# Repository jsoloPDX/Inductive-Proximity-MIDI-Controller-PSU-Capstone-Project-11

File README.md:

# MIDI-THEREMIN-Controller
A theremin style controller for MIDI devices
A Senior ECE practicum project for Portland State University

Background

Most electronic musical instruments are controlled by small motions such as knob-turns or button-pushes. Such actions tend to be neither as interesting to watch nor as expressive as, for example, a guitarist strumming or a drummer drumming (or a piper piping). Using hand gestures and arm motions to control musical instruments would allow more precise and expressive control of electronic instrument parameters. The theremin, an analog electronic instrument can be controlled by hand gestures, but it’s ability to interface with modern equipment is lacking and or restrictive.

Objective

Our objective is to update the Theremin-style analog instrument to contain digital features, mainly a MIDI output. This will allow it to expressively control all kinds of modern musical instruments and equipment.

HOW IT SHOULD WORK:
An analog theremin circuit will send proximity information to a Microcontroller. The Microcontroller will organize, process, and convert that information into MIDI data, which will be sent to a MIDI capable device VIA a standard MIDI or USB MIDI connector. There is some room for automation as far as built in “calibration” sequences to adjust the sensitivity of the coils. The device will be somewhat modular in design and construction, which will allow for expansion of the variety of proximity sensors used and versatility of output signals.

The code library "Arduino_MIDI_Library_v4.2.zip" is not our work and is taken from the project at: https://github.com/FortySevenEffects/arduino_midi_library/

The EagleCAD library "adafruit-Adafruit-Eagle-Library-4abf84c.zip" is not our work and is taken from the project at:
https://github.com/adafruit/Adafruit-Eagle-Library

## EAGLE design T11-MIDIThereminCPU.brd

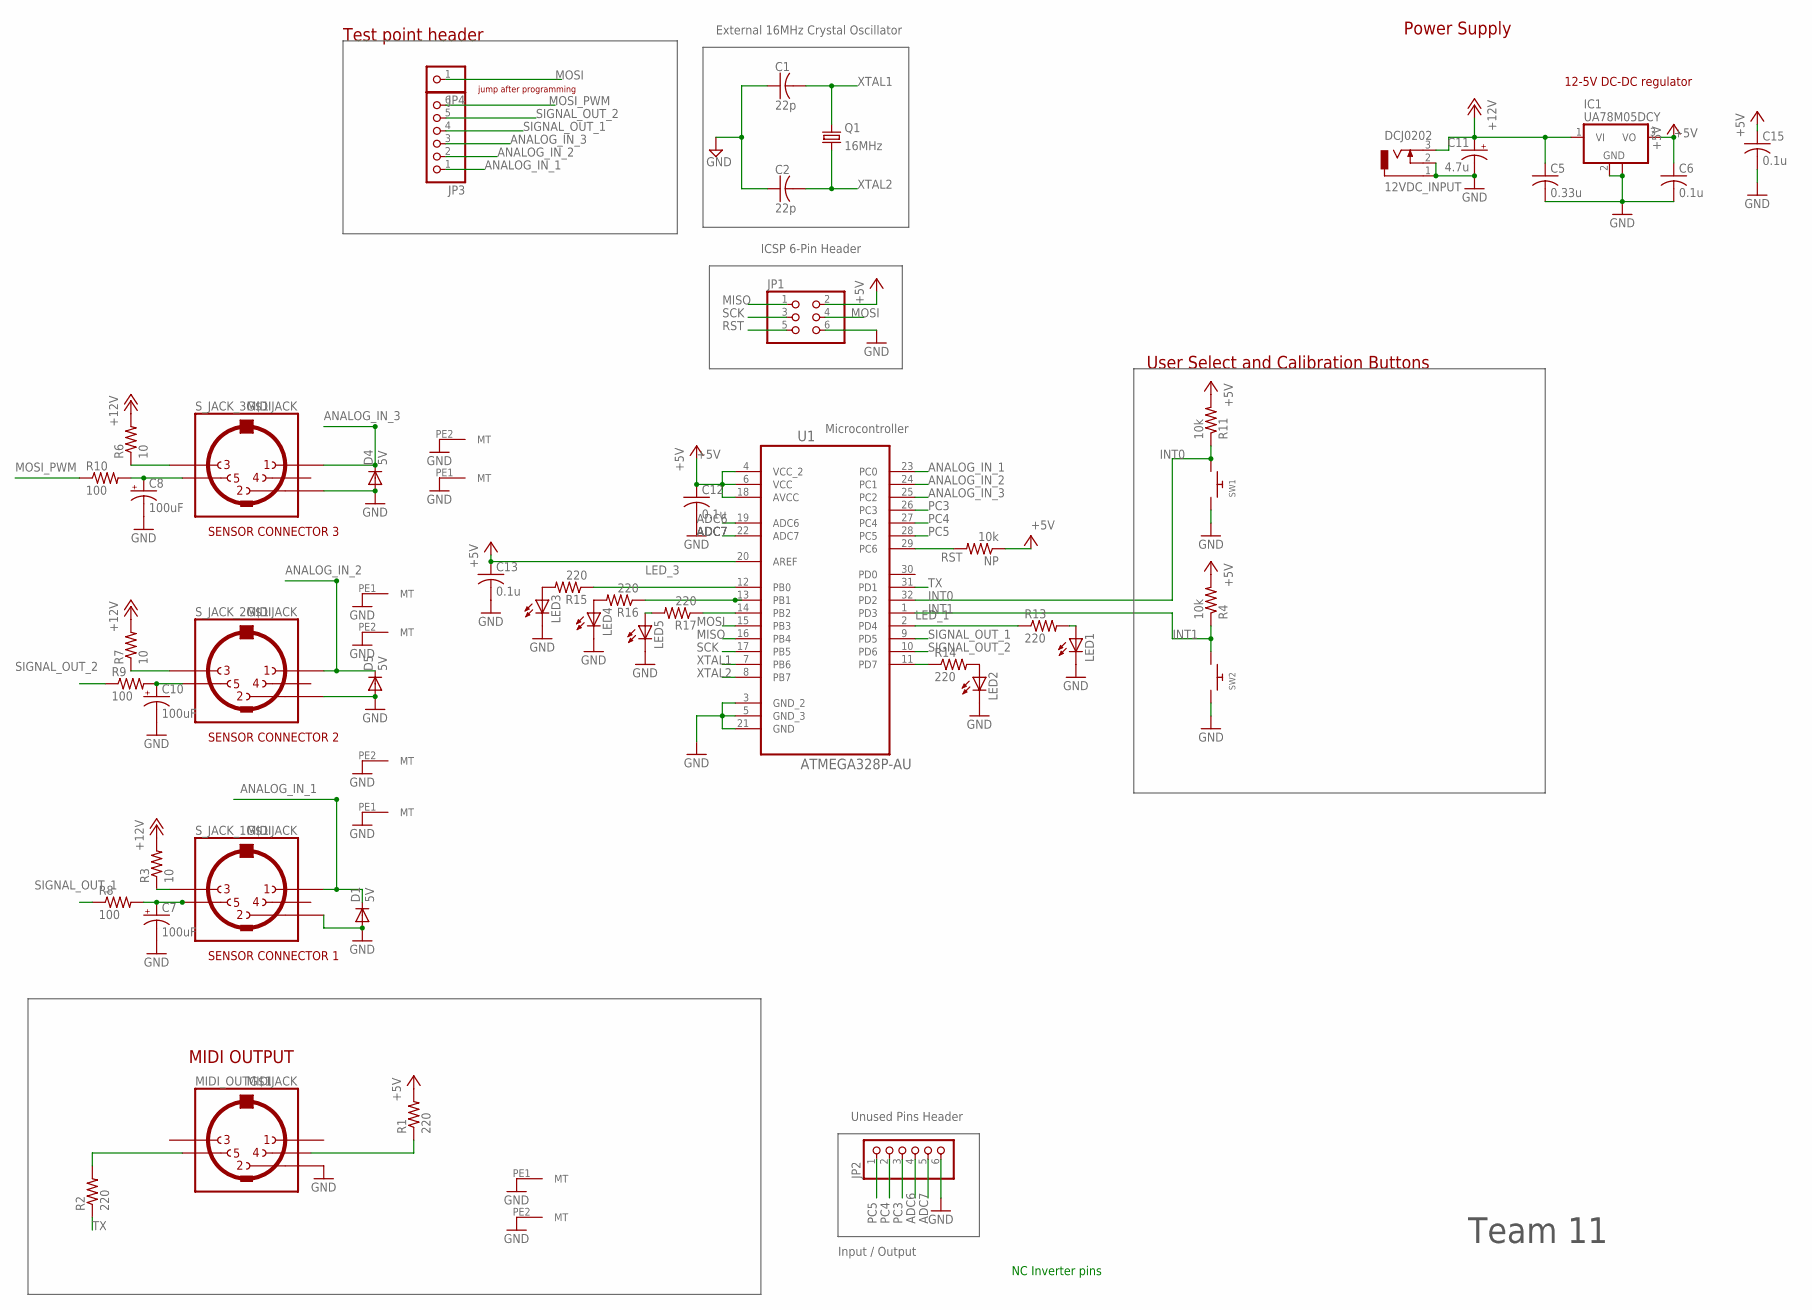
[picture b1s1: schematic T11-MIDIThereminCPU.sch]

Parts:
12VDC_INPUT: DCJ0202
C1, C2: 22p; C0805
C5: 0.33u; C0805
C6, C12, C13, C15: 0.1u; C0805
C7, C8, C10: 100uF; E3,5-8
C11: 4.7u; E3,5-8
D1, D4, D5: 5V; DO35-7
IC1: UA78M05DCY; SOT223
JP1: PINHD-2X3; 2X03
JP2, JP3: PINHD-1X6; 1X06
JP4: PINHD-1X1; 1X01
LED1, LED2, LED3, LED4, LED5: LED3MM
MIDI_OUT: MIDIJACK; CP-2350
NP: 10k; R0805
Q1: 16MHz; SM49
R1, R13, R14, R15, R16, R17: 220; R0805
R2: 220; M0805
R3, R7: 10; R0805
R4, R11: 10k; R0805
R6: 10; M0805
R8, R9: 100; R0805
R10: 100; M0805
SW1, SW2: SWITCH_PUSHBUTTONSOFTTOUCHSMD_SJ; PUSHBUTTON_SMD_SJ
S_JACK_1, S_JACK_2, S_JACK_3: MIDIJACK; CP-2350
U1: ATMEGA328P-AU; QFP80P900X900X120-32N

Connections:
+5V: C6.1, C12.1, C13.1, C15.1, IC1.3 (VO), JP1.2, NP.1, R1.2, R4.2, R11.2, U1.4 (VCC_2), U1.6 (VCC), U1.18 (AVCC), U1.20 (AREF)
+12V: 12VDC_INPUT.3, C5.1, C11.+, IC1.1 (VI), R3.2, R6.2, R7.2
ADC6: JP2.4, U1.19 (ADC6)
ADC7: JP2.5, U1.22 (ADC7)
ANALOG_IN_1: D1.C, JP3.1, S_JACK_1.1, U1.23 (PC0)
ANALOG_IN_2: D5.C, JP3.2, S_JACK_2.1, U1.24 (PC1)
ANALOG_IN_3: D4.C, JP3.3, S_JACK_3.1, U1.25 (PC2)
GND: 12VDC_INPUT.1, 12VDC_INPUT.2, C1.1, C2.1, C5.2, C6.2, C7.-, C8.-, C10.-, C11.-, C12.2, C13.2, C15.2, D1.A, D4.A, D5.A, IC1.2 (GND), IC1.4 (GND), JP1.6, JP2.6, LED1.K (C), LED2.K (C), LED3.K (C), LED4.K (C), LED5.K (C), MIDI_OUT.2, MIDI_OUT.PE1 (MT), MIDI_OUT.PE2 (MT), SW1.P$1, SW2.P$1, S_JACK_1.2, S_JACK_1.PE1 (MT), S_JACK_1.PE2 (MT), S_JACK_2.2, S_JACK_2.PE1 (MT), S_JACK_2.PE2 (MT), S_JACK_3.2, S_JACK_3.PE1 (MT), S_JACK_3.PE2 (MT), U1.3 (GND_2), U1.5 (GND_3), U1.21 (GND); also elsewhere on the board
INT0: R11.1, SW1.P$2, U1.32 (PD2); also elsewhere on the board
INT1: R4.1, SW2.P$2, U1.1 (PD3); also elsewhere on the board
LED_1: R13.1, U1.2 (PD4)
LED_2: R14.1, U1.11 (PD7)
LED_3: R15.1, U1.12 (PB0)
LED_4: R16.1, U1.13 (PB1)
LED_5: R17.1, U1.14 (PB2)
MISO: JP1.1, U1.16 (PB4)
MOSI: JP1.4, JP4.1, U1.15 (PB3)
MOSI_PWM: JP3.6, R10.1
unnamed: MIDI_OUT.4, R1.1
unnamed: C8.+, R10.2, S_JACK_3.5
unnamed: LED1.A, R13.2
unnamed: R6.1, S_JACK_3.3
unnamed: LED2.A, R14.2
unnamed: C10.+, R9.2, S_JACK_2.5
unnamed: R3.1, S_JACK_1.3
unnamed: MIDI_OUT.5, R2.2
unnamed: LED3.A, R15.2
unnamed: LED4.A, R16.2
unnamed: LED5.A, R17.2
unnamed: R7.1, S_JACK_2.3
unnamed: C7.+, R8.2, S_JACK_1.5
PC3: JP2.3, U1.26 (PC3)
PC4: JP2.2, U1.27 (PC4)
PC5: JP2.1, U1.28 (PC5)
RST: JP1.5, NP.2, U1.29 (PC6)
SCK: JP1.3, U1.17 (PB5)
SIGNAL_OUT_1: JP3.4, R8.1, U1.9 (PD5)
SIGNAL_OUT_2: JP3.5, R9.1, U1.10 (PD6)
TX: R2.1, U1.31 (PD1)
XTAL1: C1.2, Q1.2, U1.7 (PB6)
XTAL2: C2.2, Q1.1, U1.8 (PB7)

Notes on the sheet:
External 16MHz Crystal Oscillator
ICSP 6-Pin Header
Power Supply
SENSOR CONNECTOR 1
MIDI OUTPUT
Input / Output
User Select and Calibration Buttons
Unused Pins Header
Test point header
Team 11
12-5V DC-DC regulator
Microcontroller
NC Inverter pins
SENSOR CONNECTOR 2
SENSOR CONNECTOR 3
jump after programming

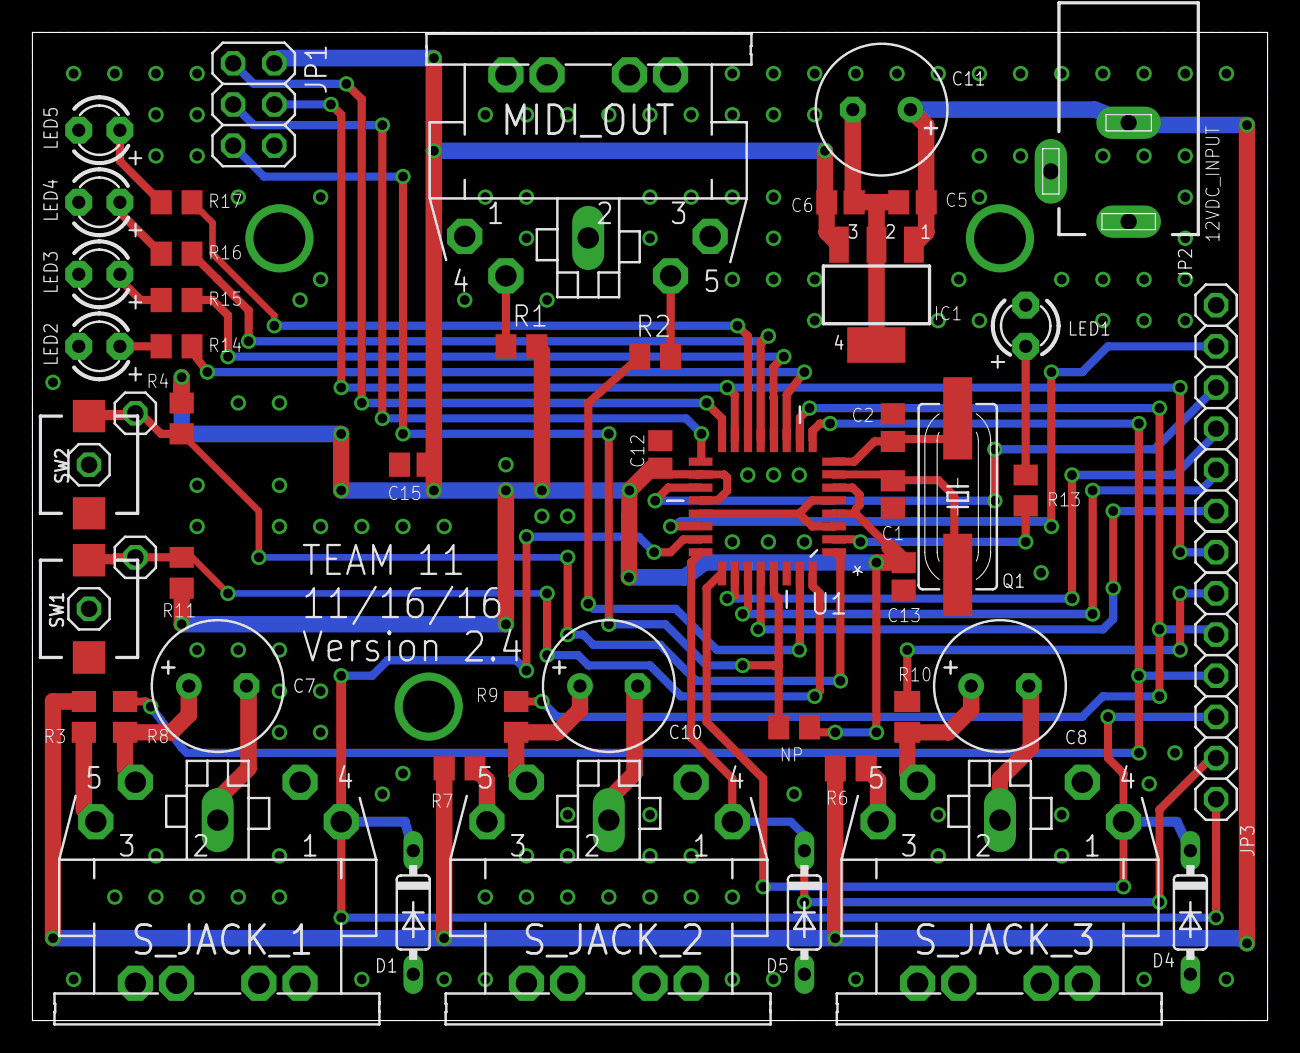
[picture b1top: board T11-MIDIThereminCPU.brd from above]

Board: 2 copper layers, 76.2 x 61.0 mm, 53 parts (0 on the bottom side), 41 nets.

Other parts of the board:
JP5, JP6, JP7, JP8: 1X01

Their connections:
GND: JP6.1, JP8.1; also elsewhere on the board
INT0: JP5.1; also elsewhere on the board
INT1: JP7.1; also elsewhere on the board

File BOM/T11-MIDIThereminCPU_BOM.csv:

"Part";"Value";"Device";"Package";"Description";"MF";"MPN";"OC_FARNELL";"OC_NEWARK";"PACKAGE";"SUPPLIER";
"12VDC_INPUT";"DCJ0202";"DCJ0202";"DCJ0202";"DC POWER JACK";"";"";"unknown";"unknown";"";"";
"C1";"22p";"C-USC0805";"C0805";"CAPACITOR, American symbol";"";"";"";"";"";"";
"C2";"22p";"C-USC0805";"C0805";"CAPACITOR, American symbol";"";"";"";"";"";"";
"C5";"0.33u";"C-USC0805";"C0805";"CAPACITOR, American symbol";"";"";"";"";"";"";
"C6";"0.1u";"C-USC0805";"C0805";"CAPACITOR, American symbol";"";"";"";"";"";"";
"C7";"100uF";"CPOL-USE3.5-8";"E3,5-8";"POLARIZED CAPACITOR, American symbol";"";"";"";"";"";"";
"C8";"100uF";"CPOL-USE3.5-8";"E3,5-8";"POLARIZED CAPACITOR, American symbol";"";"";"";"";"";"";
"C10";"100uF";"CPOL-USE3.5-8";"E3,5-8";"POLARIZED CAPACITOR, American symbol";"";"";"";"";"";"";
"C11";"4.7u";"CPOL-USE3.5-8";"E3,5-8";"POLARIZED CAPACITOR, American symbol";"";"";"";"";"";"";
"C12";"0.1u";"C-USC0805";"C0805";"CAPACITOR, American symbol";"";"";"";"";"";"";
"C13";"0.1u";"C-USC0805";"C0805";"CAPACITOR, American symbol";"";"";"";"";"";"";
"C15";"0.1u";"C-USC0805";"C0805";"CAPACITOR, American symbol";"";"";"";"";"";"";
"D1";"5V";"1N4148DO35-7";"DO35-7";"DIODE";"";"";"";"";"";"";
"D4";"5V";"1N4148DO35-7";"DO35-7";"DIODE";"";"";"";"";"";"";
"D5";"5V";"1N4148DO35-7";"DO35-7";"DIODE";"";"";"";"";"";"";
"IC1";"UA78M05DCY";"UA78M05DCY";"SOT223";"POSITIVE-VOLTAGE REGULATORS";"";"";"";"";"";"";
"JP1";"";"PINHD-2X3";"2X03";"PIN HEADER";"";"";"";"";"";"";
"JP2";"";"PINHD-1X6";"1X06";"PIN HEADER";"";"";"";"";"";"";
"JP3";"";"PINHD-1X6";"1X06";"PIN HEADER";"";"";"";"";"";"";
"JP4";"";"PINHD-1X1";"1X01";"PIN HEADER";"";"";"";"";"";"";
"JP5";"";"PINHD-1X1";"1X01";"PIN HEADER";"";"";"";"";"";"";
"JP6";"";"PINHD-1X1";"1X01";"PIN HEADER";"";"";"";"";"";"";
"JP7";"";"PINHD-1X1";"1X01";"PIN HEADER";"";"";"";"";"";"";
"JP8";"";"PINHD-1X1";"1X01";"PIN HEADER";"";"";"";"";"";"";
"LED1";"";"LED3MM";"LED3MM";"LED";"";"";"";"";"";"";
"LED2";"";"LED3MM";"LED3MM";"LED";"";"";"";"";"";"";
"LED3";"";"LED3MM";"LED3MM";"LED";"";"";"";"";"";"";
"LED4";"";"LED3MM";"LED3MM";"LED";"";"";"";"";"";"";
"LED5";"";"LED3MM";"LED3MM";"LED";"";"";"";"";"";"";
"MIDI_OUT";"MIDIJACK";"MIDIJACK";"CP-2350";"DIN 5 jack also known as MIDI jack";"";"";"";"";"";"";
"NP";"10k";"R-US_R0805";"R0805";"RESISTOR, American symbol";"";"";"";"";"";"";
"Q1";"16MHz";"CRYSTALSM49";"SM49";"CRYSTAL";"";"";"unknown";"unknown";"";"";
"R1";"220";"R-US_R0805";"R0805";"RESISTOR, American symbol";"";"";"";"";"";"";
"R2";"220";"R-US_M0805";"M0805";"RESISTOR, American symbol";"";"";"";"";"";"";
"R3";"10";"R-US_R0805";"R0805";"RESISTOR, American symbol";"";"";"";"";"";"";
"R4";"10k";"R-US_R0805";"R0805";"RESISTOR, American symbol";"";"";"";"";"";"";
"R6";"10";"R-US_M0805";"M0805";"RESISTOR, American symbol";"";"";"";"";"";"";
"R7";"10";"R-US_R0805";"R0805";"RESISTOR, American symbol";"";"";"";"";"";"";
"R8";"100";"R-US_R0805";"R0805";"RESISTOR, American symbol";"";"";"";"";"";"";
"R9";"100";"R-US_R0805";"R0805";"RESISTOR, American symbol";"";"";"";"";"";"";
"R10";"100";"R-US_M0805";"M0805";"RESISTOR, American symbol";"";"";"";"";"";"";
"R11";"10k";"R-US_R0805";"R0805";"RESISTOR, American symbol";"";"";"";"";"";"";
"R13";"220";"R-US_R0805";"R0805";"RESISTOR, American symbol";"";"";"";"";"";"";
"R14";"220";"R-US_R0805";"R0805";"RESISTOR, American symbol";"";"";"";"";"";"";
"R15";"220";"R-US_R0805";"R0805";"RESISTOR, American symbol";"";"";"";"";"";"";
"R16";"220";"R-US_R0805";"R0805";"RESISTOR, American symbol";"";"";"";"";"";"";
"R17";"220";"R-US_R0805";"R0805";"RESISTOR, American symbol";"";"";"";"";"";"";
"SW1";"";"SWITCH_PUSHBUTTONSOFTTOUCHSMD_SJ";"PUSHBUTTON_SMD_SJ";"Buttons";"";"";"";"";"";"";
"SW2";"";"SWITCH_PUSHBUTTONSOFTTOUCHSMD_SJ";"PUSHBUTTON_SMD_SJ";"Buttons";"";"";"";"";"";"";
"S_JACK_1";"MIDIJACK";"MIDIJACK";"CP-2350";"DIN 5 jack also known as MIDI jack";"";"";"";"";"";"";
"S_JACK_2";"MIDIJACK";"MIDIJACK";"CP-2350";"DIN 5 jack also known as MIDI jack";"";"";"";"";"";"";
"S_JACK_3";"MIDIJACK";"MIDIJACK";"CP-2350";"DIN 5 jack also known as MIDI jack";"";"";"";"";"";"";
"U1";"ATMEGA328P-AU";"ATMEGA328P-AU";"QFP80P900X900X120-32N";"8-bit Microcontroller with In-System Programmable Flash";"";"ATMEGA328P-AU";"1715486";"14R4631";"TQFP-32";"Atmel";

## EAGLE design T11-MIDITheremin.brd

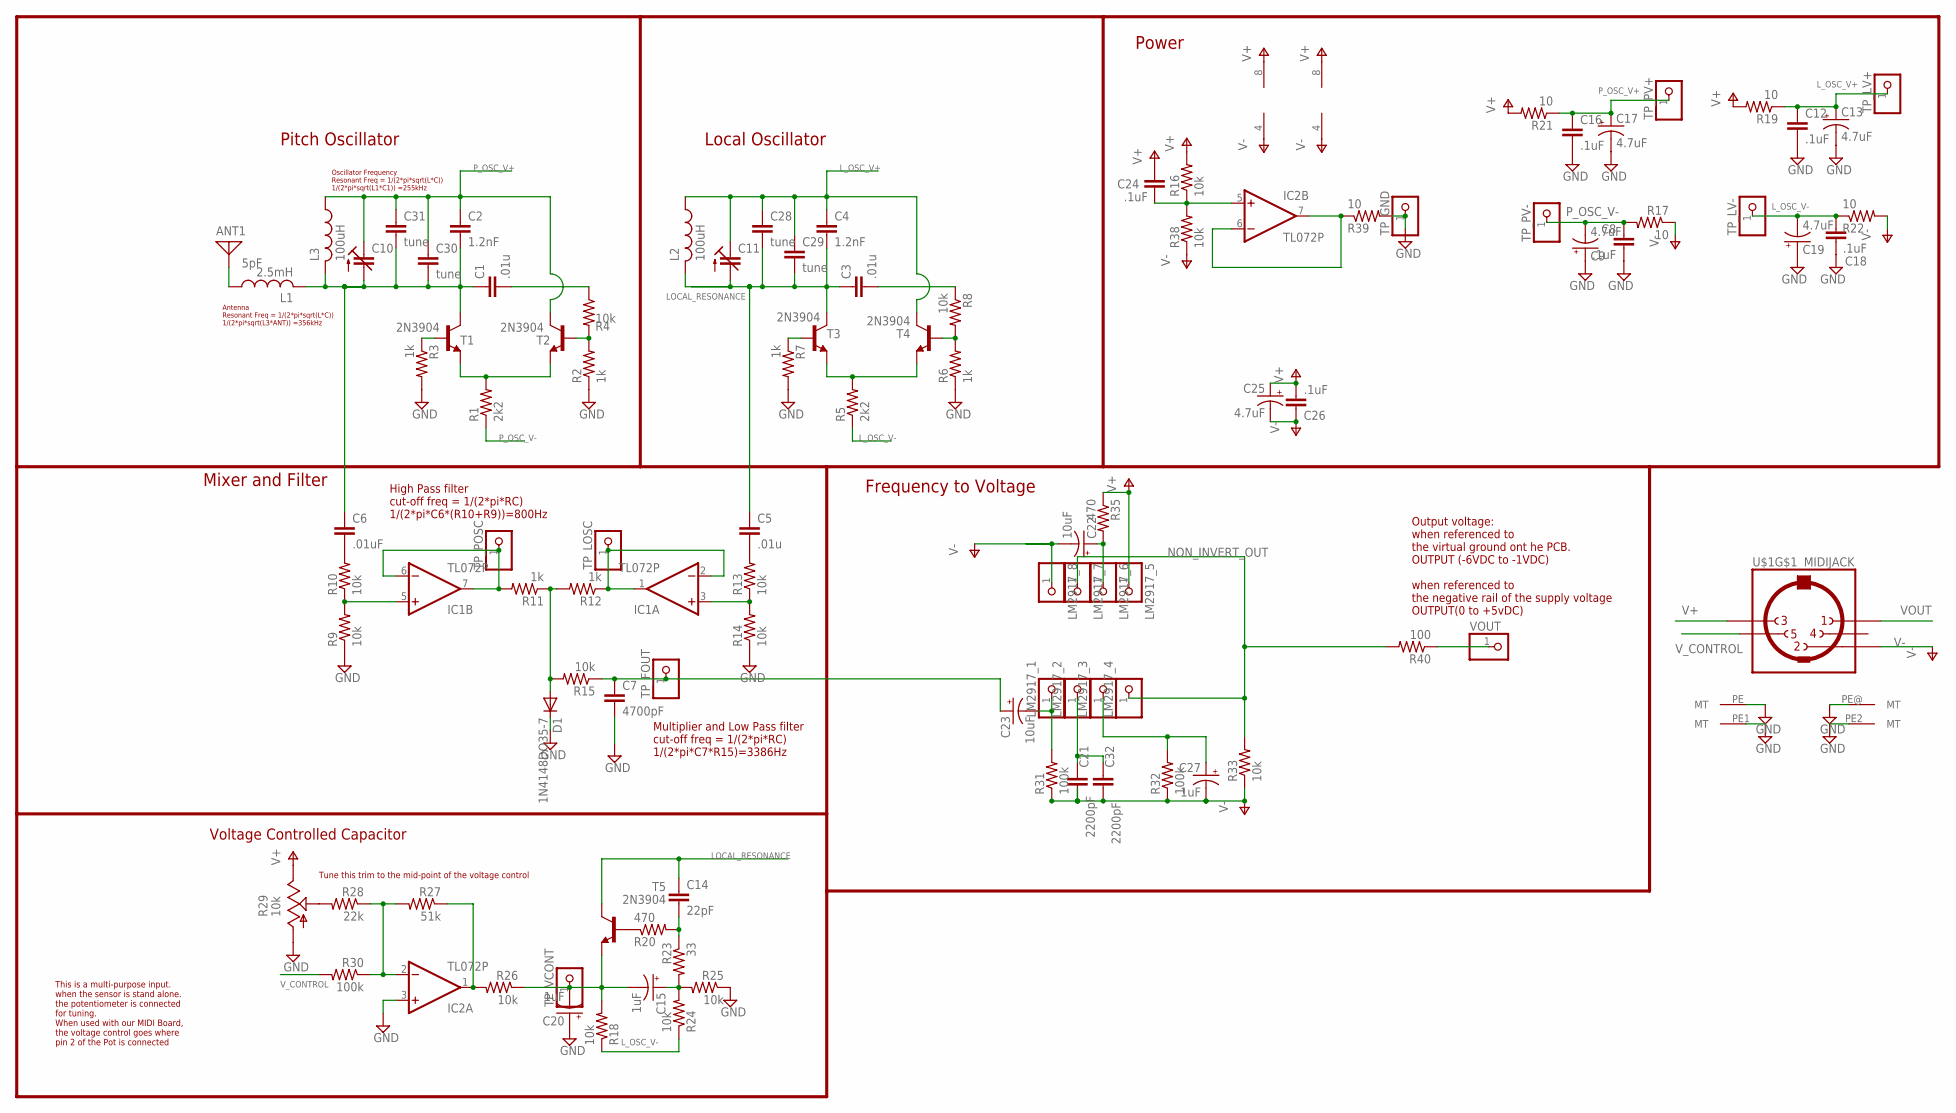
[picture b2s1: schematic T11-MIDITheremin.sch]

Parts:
ANT1: 5pF; PAD-01
C1, C3, C5: .01u; C050-025X075
C2, C4: 1.2nF; C050-025X075
C6: .01uF; C050-025X075
C7: 4700pF; C050-025X075
C8, C12, C16, C18, C24, C26: .1uF; C050-025X075
C9, C13, C17, C19, C25: 4.7uF; E2,5-7
C10, C11: C-TRIMM3040.427; CTRIM3040.427
C14: 22pF; C050-025X075
C15, C20, C27: 1uF; E2,5-7
C21, C32: 2200pF; C050-025X075
C22, C23: 10uF; E2,5-7
C28, C29, C30, C31: tune; C050-025X075
D1: 1N4148DO35-7; DO35-7
IC1, IC2: TL072P; DIL08
L1: 2.5mH; 0207/5V
L2, L3: 100uH; 0207/5V
LM2917_1, LM2917_2, LM2917_3, LM2917_4, LM2917_5, LM2917_6, LM2917_7, LM2917_8: PINHD-1X1; 1X01
R1, R5: 2k2; 0411V
R2, R3, R6, R7, R11, R12: 1k; 0411V
R4, R8, R9, R10, R13, R14, R15, R16, R18, R24, R25, R26, R33, R38: 10k; 0411V
R17, R19, R21, R22, R39: 10; 0411V
R20, R35: 470; 0411V
R23: 33; 0411V
R27: 51k; 0411V
R28: 22k; 0411V
R29: 10k; B64Y
R30, R31, R32: 100k; 0411V
R40: 100; 0411V
T1, T2, T3, T4, T5: 2N3904; TO92
TP_FOUT: PINHD-1X1; 1X01
TP_GND: PINHD-1X1; 1X01
TP_LOSC: PINHD-1X1; 1X01
TP_LV+: PINHD-1X1; 1X01
TP_LV-: PINHD-1X1; 1X01
TP_POSC: PINHD-1X1; 1X01
TP_PV+: PINHD-1X1; 1X01
TP_PV-: PINHD-1X1; 1X01
TP_VCONT: PINHD-1X1; 1X01
U$1: MIDIJACK; CP-2350
VOUT: PINHD-1X1; 1X01

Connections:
GND: C7.2, C8.2, C9.+, C12.2, C13.-, C16.2, C17.-, C18.2, C19.+, C20.+, D1.C, IC2.3 (+IN), R2.1, R3.2, R6.1, R7.2, R9.1, R14.1, R25.1, R29.A, R39.2, TP_GND.1, U$1.PE (MT), U$1.PE1 (MT), U$1.PE2 (MT), U$1.PE@ (MT)
LOCAL_RESONANCE: C3.1, C4.2, C5.1, C11.2 (A), C14.1, C28.2, C29.2, L2.2, T3.1 (C), T5.1 (C)
L_OSC_V+: C4.1, C11.1A (E), C12.1, C13.+, C28.1, C29.1, L2.1, R19.1, T4.1 (C), TP_LV+.1
L_OSC_V-: C18.1, C19.-, R5.1, R18.1, R22.1, R24.1, TP_LV-.1
unnamed: R1.2, T1.3 (E), T2.3 (E)
unnamed: R2.2, R4.2, T2.2 (B)
unnamed: R3.1, T1.2 (B)
unnamed: C1.1, C2.2, C6.1, C10.2 (A), C30.2, C31.2, L1.2, L3.2, T1.1 (C)
unnamed: C1.2, R4.1
unnamed: R5.2, T3.3 (E), T4.3 (E)
unnamed: R6.2, R8.2, T4.2 (B)
unnamed: R7.1, T3.2 (B)
unnamed: C15.-, C20.-, R18.2, R26.1, T5.3 (E), TP_VCONT.1
unnamed: C5.2, R13.2
unnamed: IC1.6 (-IN), IC1.7 (OUT), R11.2, TP_POSC.1
unnamed: IC1.1 (OUT), IC1.2 (-IN), R12.1, TP_LOSC.1
unnamed: IC1.5 (+IN), R9.2, R10.1
unnamed: D1.A, R11.1, R12.2, R15.2
unnamed: IC1.3 (+IN), R13.1, R14.2
unnamed: C3.2, R8.1
unnamed: C6.2, R10.2
unnamed: C7.1, C23.+, R15.1, TP_FOUT.1
unnamed: C21.1, C32.1, LM2917_2.1
unnamed: R20.1, T5.2 (B)
unnamed: C14.2, R20.2, R23.1
unnamed: C15.+, R23.2, R24.2, R25.2
unnamed: IC2.1 (OUT), R26.2, R27.1
unnamed: IC2.2 (-IN), R27.2, R28.1, R30.1
unnamed: R28.2, R29.S
unnamed: IC2.6 (-IN), IC2.7 (OUT), R39.1
unnamed: ANT1.1, L1.1
unnamed: C22.+, LM2917_6.1, R35.2
unnamed: C27.+, LM2917_3.1, R32.2
unnamed: C23.-, LM2917_1.1, R31.2
unnamed: C24.2, IC2.5 (+IN), R16.1, R38.2
NON_INVERT_OUT: LM2917_4.1, LM2917_7.1, R33.2, R40.2
P_OSC_V+: C2.1, C10.1A (E), C16.1, C17.+, C30.1, C31.1, L3.1, R21.1, T2.1 (C), TP_PV+.1
P_OSC_V-: C8.1, C9.-, R1.1, R17.2, TP_PV-.1
V+: C24.1, C25.+, C26.2, IC1.8 (V+), IC2.8 (V+), LM2917_5.1, R16.2, R19.2, R21.2, R29.E, R35.1, U$1.3
V-: C21.2, C22.-, C25.-, C26.1, C27.-, C32.2, IC1.4 (V-), IC2.4 (V-), LM2917_8.1, R17.1, R22.2, R31.1, R32.1, R33.1, R38.1, U$1.2
VOUT: R40.1, U$1.1, VOUT.1
V_CONTROL: R30.2, U$1.5

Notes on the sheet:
Pitch Oscillator
Local Oscillator
High Pass filter cut-off freq = 1/(2*pi*RC) 1/(2*pi*C6*(R10+R9))=800Hz
Multiplier and Low Pass filter cut-off freq = 1/(2*pi*RC) 1/(2*pi*C7*R15)=3386Hz
Oscillator Frequency Resonant Freq = 1/(2*pi*sqrt(L*C)) 1/(2*pi*sqrt(L1*C1)) =255kHz
Antenna Resonant Freq = 1/(2*pi*sqrt(L*C)) 1/(2*pi*sqrt(L3*ANT)) =356kHz
Mixer and Filter
Frequency to Voltage
Voltage Controlled Capacitor
Power
Tune this trim to the mid-point of the voltage control
This is a multi-purpose input. when the sensor is stand alone. the potentiometer is connected for tuning. When used with our MIDI Board, the voltage control goes where pin 2 of the Pot is connected
Output voltage: when referenced to the virtual ground ont he PCB. OUTPUT (-6VDC to -1VDC) when referenced to the negative rail of the supply voltage OUTPUT(0 to +5vDC)

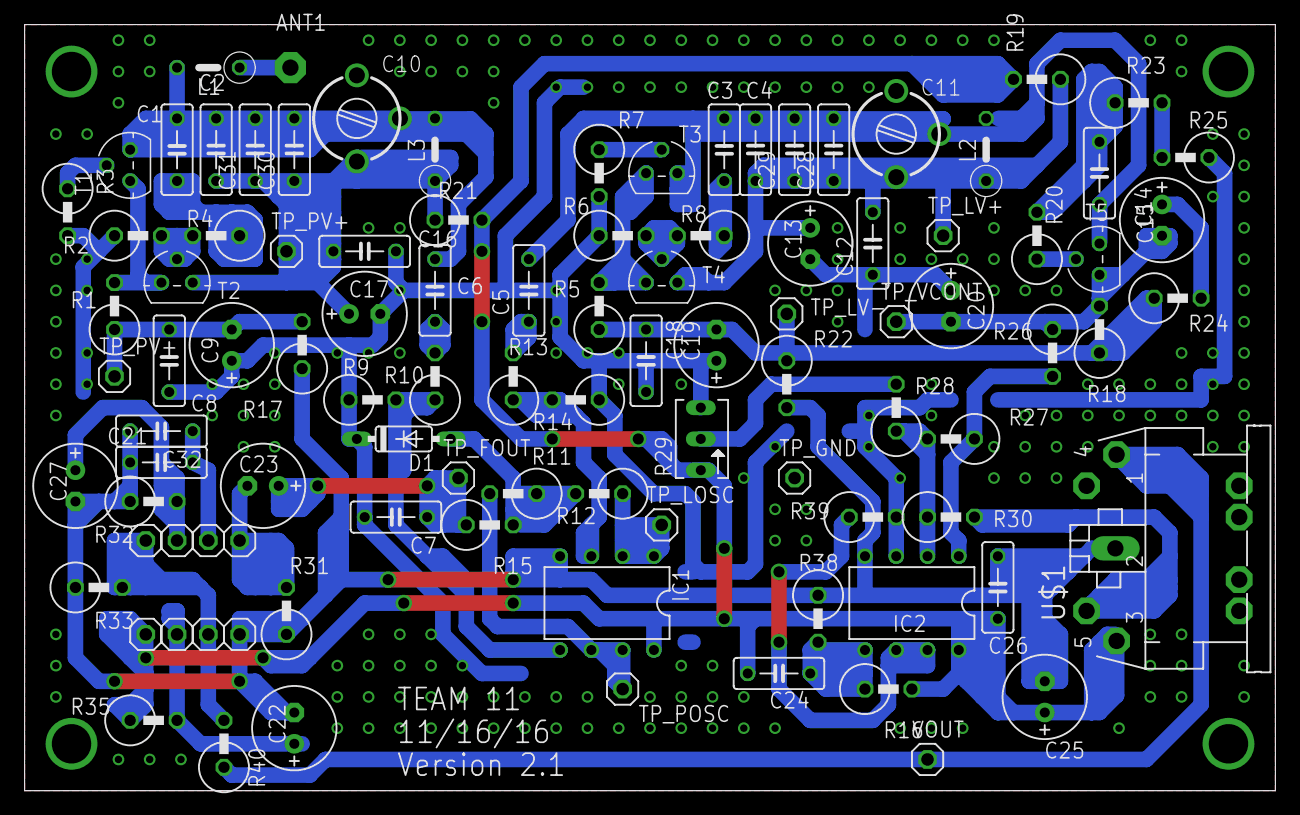
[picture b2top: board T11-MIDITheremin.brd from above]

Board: 2 copper layers, 101.6 x 62.2 mm, 100 parts (0 on the bottom side), 42 nets.

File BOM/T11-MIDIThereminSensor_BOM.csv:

"Part";"Value";"Device";"Package";"Description";"";
"ANT1";"5pF";"ANTENNA";"PAD-01";"Antenna";"";
"C1";".01u";"C-EU050-025X075";"C050-025X075";"CAPACITOR, European symbol";"";
"C2";"1.2nF";"C-EU050-025X075";"C050-025X075";"CAPACITOR, European symbol";"";
"C3";".01u";"C-EU050-025X075";"C050-025X075";"CAPACITOR, European symbol";"";
"C4";"1.2nF";"C-EU050-025X075";"C050-025X075";"CAPACITOR, European symbol";"";
"C5";".01u";"C-EU050-025X075";"C050-025X075";"CAPACITOR, European symbol";"";
"C6";".01uF";"C-EU050-025X075";"C050-025X075";"CAPACITOR, European symbol";"";
"C7";"4700pF";"C-EU050-025X075";"C050-025X075";"CAPACITOR, European symbol";"";
"C8";".1uF";"C-EU050-025X075";"C050-025X075";"CAPACITOR, European symbol";"";
"C9";"4.7uF";"CPOL-USE2.5-7";"E2,5-7";"POLARIZED CAPACITOR, American symbol";"";
"C10";"";"C-TRIMM3040.427";"CTRIM3040.427";"Trimm capacitor";"";
"C11";"";"C-TRIMM3040.427";"CTRIM3040.427";"Trimm capacitor";"";
"C12";".1uF";"C-EU050-025X075";"C050-025X075";"CAPACITOR, European symbol";"";
"C13";"4.7uF";"CPOL-USE2.5-7";"E2,5-7";"POLARIZED CAPACITOR, American symbol";"";
"C14";"22pF";"C-EU050-025X075";"C050-025X075";"CAPACITOR, European symbol";"";
"C15";"1uF";"CPOL-USE2.5-7";"E2,5-7";"POLARIZED CAPACITOR, American symbol";"";
"C16";".1uF";"C-EU050-025X075";"C050-025X075";"CAPACITOR, European symbol";"";
"C17";"4.7uF";"CPOL-USE2.5-7";"E2,5-7";"POLARIZED CAPACITOR, American symbol";"";
"C18";".1uF";"C-EU050-025X075";"C050-025X075";"CAPACITOR, European symbol";"";
"C19";"4.7uF";"CPOL-USE2.5-7";"E2,5-7";"POLARIZED CAPACITOR, American symbol";"";
"C20";"1uF";"CPOL-USE2.5-7";"E2,5-7";"POLARIZED CAPACITOR, American symbol";"";
"C21";"3900pF";"C-EU050-025X075";"C050-025X075";"CAPACITOR, European symbol";"";
"C22";"10uF";"CPOL-USE2.5-7";"E2,5-7";"POLARIZED CAPACITOR, American symbol";"";
"C23";"10uF";"CPOL-USE2.5-7";"E2,5-7";"POLARIZED CAPACITOR, American symbol";"";
"C24";".1uF";"C-EU050-025X075";"C050-025X075";"CAPACITOR, European symbol";"";
"C25";"4.7uF";"CPOL-USE2.5-7";"E2,5-7";"POLARIZED CAPACITOR, American symbol";"";
"C26";".1uF";"C-EU050-025X075";"C050-025X075";"CAPACITOR, European symbol";"";
"C27";"1uF";"CPOL-USE2.5-7";"E2,5-7";"POLARIZED CAPACITOR, American symbol";"";
"C28";"tune";"C-EU050-025X075";"C050-025X075";"CAPACITOR, European symbol";"";
"C29";"tune";"C-EU050-025X075";"C050-025X075";"CAPACITOR, European symbol";"";
"C30";"tune";"C-EU050-025X075";"C050-025X075";"CAPACITOR, European symbol";"";
"C31";"tune";"C-EU050-025X075";"C050-025X075";"CAPACITOR, European symbol";"";
"C32";"3900pF";"C-EU050-025X075";"C050-025X075";"CAPACITOR, European symbol";"";
"D1";"1N4148DO35-7";"1N4148DO35-7";"DO35-7";"DIODE";"";
"IC1";"TL072P";"TL072P";"DIL08";"OP AMP";"";
"IC2";"TL072P";"TL072P";"DIL08";"OP AMP";"";
"L1";"2.5mH";"L-US0207/5V";"0207/5V";"INDUCTOR, American symbol";"";
"L2";"100uH";"L-US0207/5V";"0207/5V";"INDUCTOR, American symbol";"";
"L3";"100uH";"L-US0207/5V";"0207/5V";"INDUCTOR, American symbol";"";
"LM2917_1";"";"PINHD-1X1";"1X01";"PIN HEADER";"";
"LM2917_2";"";"PINHD-1X1";"1X01";"PIN HEADER";"";
"LM2917_3";"";"PINHD-1X1";"1X01";"PIN HEADER";"";
"LM2917_4";"";"PINHD-1X1";"1X01";"PIN HEADER";"";
"LM2917_5";"";"PINHD-1X1";"1X01";"PIN HEADER";"";
"LM2917_6";"";"PINHD-1X1";"1X01";"PIN HEADER";"";
"LM2917_7";"";"PINHD-1X1";"1X01";"PIN HEADER";"";
"LM2917_8";"";"PINHD-1X1";"1X01";"PIN HEADER";"";
"PROXIMITY";"";"PINHD-1X1";"1X01";"PIN HEADER";"";
"R1";"2k2";"R-US_0411/3V";"0411V";"RESISTOR, American symbol";"";
"R2";"1k";"R-US_0411/3V";"0411V";"RESISTOR, American symbol";"";
"R3";"1k";"R-US_0411/3V";"0411V";"RESISTOR, American symbol";"";
"R4";"10k";"R-US_0411/3V";"0411V";"RESISTOR, American symbol";"";
"R5";"2k2";"R-US_0411/3V";"0411V";"RESISTOR, American symbol";"";
"R6";"1k";"R-US_0411/3V";"0411V";"RESISTOR, American symbol";"";
"R7";"1k";"R-US_0411/3V";"0411V";"RESISTOR, American symbol";"";
"R8";"10k";"R-US_0411/3V";"0411V";"RESISTOR, American symbol";"";
"R9";"10k";"R-US_0411/3V";"0411V";"RESISTOR, American symbol";"";
"R10";"10k";"R-US_0411/3V";"0411V";"RESISTOR, American symbol";"";
"R11";"1k";"R-US_0411/3V";"0411V";"RESISTOR, American symbol";"";
"R12";"1k";"R-US_0411/3V";"0411V";"RESISTOR, American symbol";"";
"R13";"10k";"R-US_0411/3V";"0411V";"RESISTOR, American symbol";"";
"R14";"10k";"R-US_0411/3V";"0411V";"RESISTOR, American symbol";"";
"R15";"10k";"R-US_0411/3V";"0411V";"RESISTOR, American symbol";"";
"R16";"10k";"R-US_0411/3V";"0411V";"RESISTOR, American symbol";"";
"R17";"10";"R-US_0411/3V";"0411V";"RESISTOR, American symbol";"";
"R18";"10k";"R-US_0411/3V";"0411V";"RESISTOR, American symbol";"";
"R19";"10";"R-US_0411/3V";"0411V";"RESISTOR, American symbol";"";
"R20";"470";"R-US_0411/3V";"0411V";"RESISTOR, American symbol";"";
"R21";"10";"R-US_0411/3V";"0411V";"RESISTOR, American symbol";"";
"R22";"10";"R-US_0411/3V";"0411V";"RESISTOR, American symbol";"";
"R23";"33";"R-US_0411/3V";"0411V";"RESISTOR, American symbol";"";
"R24";"10k";"R-US_0411/3V";"0411V";"RESISTOR, American symbol";"";
"R25";"10k";"R-US_0411/3V";"0411V";"RESISTOR, American symbol";"";
"R26";"10k";"R-US_0411/3V";"0411V";"RESISTOR, American symbol";"";
"R27";"51k";"R-US_0411/3V";"0411V";"RESISTOR, American symbol";"";
"R28";"22k";"R-US_0411/3V";"0411V";"RESISTOR, American symbol";"";
"R29";"10k";"TRIM_US-B64Y";"B64Y";"POTENTIOMETER";"";
"R30";"100k";"R-US_0411/3V";"0411V";"RESISTOR, American symbol";"";
"R31";"100k";"R-US_0411/3V";"0411V";"RESISTOR, American symbol";"";
"R32";"100k";"R-US_0411/3V";"0411V";"RESISTOR, American symbol";"";
"R33";"10k";"R-US_0411/3V";"0411V";"RESISTOR, American symbol";"";
"R35";"470";"R-US_0411/3V";"0411V";"RESISTOR, American symbol";"";
"R38";"10k";"R-US_0411/3V";"0411V";"RESISTOR, American symbol";"";
"R39";"10";"R-US_0411/3V";"0411V";"RESISTOR, American symbol";"";
"R40";"100";"R-US_0411/3V";"0411V";"RESISTOR, American symbol";"";
"S_JACK";"MIDIJACK";"MIDIJACK";"CP-2350";"DIN 5 jack also known as MIDI jack";"";
"T1";"2N3904";"2N3904";"TO92";"NPN TRANSISTOR";"";
"T2";"2N3904";"2N3904";"TO92";"NPN TRANSISTOR";"";
"T3";"2N3904";"2N3904";"TO92";"NPN TRANSISTOR";"";
"T4";"2N3904";"2N3904";"TO92";"NPN TRANSISTOR";"";
"T5";"2N3904";"2N3904";"TO92";"NPN TRANSISTOR";"";
"TP_FOUT";"";"PINHD-1X1";"1X01";"PIN HEADER";"";
"TP_GND";"";"PINHD-1X1";"1X01";"PIN HEADER";"";
"TP_LOSC";"";"PINHD-1X1";"1X01";"PIN HEADER";"";
"TP_LV+";"";"PINHD-1X1";"1X01";"PIN HEADER";"";
"TP_LV-";"";"PINHD-1X1";"1X01";"PIN HEADER";"";
"TP_POSC";"";"PINHD-1X1";"1X01";"PIN HEADER";"";
"TP_PV+";"";"PINHD-1X1";"1X01";"PIN HEADER";"";
"TP_PV-";"";"PINHD-1X1";"1X01";"PIN HEADER";"";
"TP_VCONT";"";"PINHD-1X1";"1X01";"PIN HEADER";"";

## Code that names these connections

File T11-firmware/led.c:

void BlinkLED_PD4(unsigned char NumOfBlinks){

	unsigned char i = 0;
	for (i = 0; i < NumOfBlinks; i++){ 	
		// Set PD4 port as on
		PORTD |= (1 << DDD4);
		_delay_ms(DelayOn);
		
		// Set PD4 port as off
		PORTD &= ~(1<<DDD4);
		_delay_ms(DelayOff);
	}
}




void BlinkLED_PD7(unsigned char NumOfBlinks){

	unsigned char i = 0;
	for (i = 0; i < NumOfBlinks; i++){ 	
		// Set PD7 port as on
		PORTD |= (1 << DDD7);
		_delay_ms(DelayOn);
		
		// Set PD7 port as off
		PORTD &= ~(1<<DDD7);
		_delay_ms(DelayOff);

	}
}




void BlinkLED_PB0(unsigned char NumOfBlinks){

	unsigned char i = 0;
	for (i = 0; i < NumOfBlinks; i++){ 	
		// Set PB0 port as on
		PORTB |= (1 << DDB0);
		_delay_ms(DelayOn);
		
		// Set PB0 port as off
		PORTB &= ~(1<<DDB0);
		_delay_ms(DelayOff);
	}
}





void BlinkLED_PB1(unsigned char NumOfBlinks){

	unsigned char i = 0;
	for (i = 0; i < NumOfBlinks; i++){ 	
		// Set PB1 port as on
		PORTB |= (1 << DDB1);
		_delay_ms(DelayOn);
		
		// Set PB1 port as off
		PORTB &= ~(1<<DDB1);
		_delay_ms(DelayOff);
	}
}




void BlinkLED_PB2(unsigned char NumOfBlinks){

	unsigned char i = 0;
	for (i = 0; i < NumOfBlinks; i++){ 	
		// Set PB2 port as on
		PORTB |= (1 << DDB2);
		_delay_ms(DelayOn);
		
		// Set PB2 port as off
		PORTB &= ~(1<<DDB2);
		_delay_ms(DelayOff);
	}
}


void LED_ON_All(void)
{
	PORTD |= (1 << DDD4);
	PORTD |= (1 << DDD7);
	PORTB |= (1 << DDB0);
	PORTB |= (1 << DDB1);
	PORTB |= (1 << DDB2);
}

void LED_OFF_All(void)
{
	PORTD &= ~(1<<DDD4);
	PORTD &= ~(1<<DDD7);
	PORTB &= ~(1 << DDB0);
	PORTB &= ~(1<<DDB1);
	PORTB &= ~(1<<DDB2); 
}

void LED_ON_One(void)
{
	PORTD &= ~(1<<DDD4);
	PORTD &= ~(1<<DDD7);
	PORTB |= (1 << DDB0);
	PORTB &= ~(1<<DDB1);
	PORTB &= ~(1<<DDB2); 
}

void LED_ON_Two(void)
{
	PORTD &= ~(1<<DDD4);
	PORTD &= ~(1<<DDD7);
	PORTB |= (1 << DDB0);
	PORTB |= (1 << DDB1);
	PORTB &= ~(1<<DDB2);
}

void LED_ON_Three(void)
{
	PORTD &= ~(1<<DDD4);
	PORTD &= ~(1<<DDD7);
	PORTB |= (1 << DDB0);
	PORTB |= (1 << DDB1);
	PORTB |= (1 << DDB2);
}


void LED_ON_Power(void)
{
	PORTD |= (1 << DDD4);
	PORTD &= ~(1<<DDD7);
	PORTB &= ~(1<<DDB0);
	PORTB &= ~(1<<DDB1);
	PORTB &= ~(1<<DDB2);
}

void LED_ON_Power_One(void)
{
	PORTD |= (1 << DDD4);
	PORTD &= ~(1<<DDD7);
	PORTB |= (1<<DDB0);
	PORTB &= ~(1<<DDB1);
	PORTB &= ~(1<<DDB2);
}

void LED_ON_Power_Two(void)
{
	PORTD |= (1 << DDD4);
	PORTD &= ~(1<<DDD7);
	PORTB |= (1 << DDB0);
	PORTB |= (1 << DDB1);
	PORTB &= ~(1<<DDB2);
}

void LED_ON_Power_Three(void)
{
	PORTD |= (1 << DDD4);
	PORTD &= ~(1<<DDD7);
	PORTB |= (1 << DDB0);
	PORTB |= (1 << DDB1);
	PORTB |= (1 << DDB2);
}

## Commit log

2016-10-20 Example code
    Example code to evaluate how GitHub works
2016-10-20 Update example_code.ino
    added some lines
2016-10-20 Created a branch and pull
    changed a value and chose create a new branch and start a pull request
2016-10-24 Delete example_code.ino
    Deleted unnecessary file
2016-10-24 Added MIDI Library Files
    We will probably need these as part of our overall project. I will update the readme to point out that this is not our code
2016-10-24 Update README.md
    Added a line giving credit to the creators of the MIDI library
2016-10-25 Add files via upload
    Updated schematic to include frequency to voltage circuit
2016-10-26 Create UserFunctionality document
    This document begins the discussion about how the user will interface with the controller
2016-10-28 Add files via upload
    Started a parts list
2016-10-28 Added MIDI_Init function. Also, testing Git functionality.
2016-10-28 These are updated Schematics
    updated schematic and PCB
2016-10-30 Update README.md
    changed out to our in line 7
2016-10-30 Added power input
    Added DC barrel jack and 5v and 3.3v regulated sources
2016-11-01 Added library with MIDI jack
2016-11-01 Update README.md
    attributed the adafruit EagleCAD library to creators
2016-11-01 Labeled power section and added MIDI I/O
2016-11-01 Add files via upload
    EagleCAD Library with zener symbols
2016-11-01 Removed 3.3V, connected MIDI
2016-11-01 Update README.md
    attributed the sparkfun library to creators
2016-11-02 Added LED and push button, MIDI hookup refinement.
    Added a 7-seg LED display and debounced push button. Grounded MIDI shields and added optional ferrite beads to MIDI out as per MIDI 2014 specifications.
2016-11-02 Rename SparkFun-DiscreteSemi.lbr to Outside-Code/SparkFun-DiscreteSemi.lbr
    created outside code folder
2016-11-02 Moved code
    Moved outside code into outside code folder
2016-11-02 Fixed some part connections
    Changed midi output signals from pins 1 and 3 to 4 and 5. Reversed orientation of zener diode on MIDI in.
2016-11-03 Added LEDs, button 2, midi jacks
    Removed the 7-segement LED and replaced it with 5 LEDs, added a second debounced button, added 2 more midi jacks to sensor board connections.
2016-11-03 Changes per discussion
2016-11-03 changes per discussion
    added test points and unused pin headers. pull up resistor on reset. are +5V. barrel jack wired correctly.
2016-11-03 renamed theremin boards
2016-11-03 Drew connections
    Drew in the connections. These look horrible and only connect to labeled points on the arduino, so I don't see the point but oh well.
2016-11-04 Added PWM support for PD5 and PD6.
2016-11-04 Appended T11- to files.
2016-11-05 Added amplifiers
    Added adjustable amplification onto the return signal from sensor
    board. Named ICs. Some rearrangement.
2016-11-07 Add files via upload
    Added due dates
2016-11-08 made discussed changes
2016-11-08 Added ferrite bead values
2016-11-08 Updated Gantt chart
2016-11-09 Changed filter values
2016-11-10 Some Package Changes
2016-11-10 Initial
2016-11-10 Board creation
2016-11-10 Changed resistors and caps to smd
2016-11-10 block diagram
2016-11-10 Improved routing, coupling caps added
2016-11-10 Improved routing, added coupling caps
2016-11-10 Fixed DRC errors
2016-11-10 Updated CPU board progress
2016-11-10 Created documentation folder
2016-11-10 Added preview folder
2016-11-11 Added PWM support for PB3. Wrote functions to allow change of PWM Duty Cycle, to avoid redundant initialization of the ports.
2016-11-11 Add files via upload
    still needs a board name
2016-11-14 Created BOM, updated parts
2016-11-14 updated cpu preview
2016-11-14 updated preview
2016-11-14 weekly update
2016-11-14 rename file
2016-11-14 Removed option to change frequency due to issues. Will re-implement if it becomes necessary. Currently, PWM is set to around 8 kHz.
2016-11-15 Changed PWM frequency back.
2016-11-15 Updated frequency to 8kHz.
2016-11-15 Add files via upload
    added main.c
2016-11-16 Fixed ERC errors. Added revision and date to CPU schematic.
2016-11-16 Fixed Unrouted wires. Added Team Number and Revision.
2016-11-16 Added date to CPU Board. Removed b#x and s#x files.
2016-11-16 added a jumper to the MOSI line for programming
2016-11-17 removed debounce circuit. added vias
2016-11-17 added optional panel mount buttons
2016-11-17 fixed some of the silkscreen layer
2016-11-17 Update from weekly progress reports
2016-11-18 Upload
2016-11-18 Updated previews
2016-11-18 Fixed rotation
2016-11-20 undeeded
2016-11-21 Updated Gantt from progress reports
2016-11-21 Cleared main.c of testing code, and setup some of the program skeleton.
2016-11-22 Added code for button presses, and for one of the LEDs.
2016-11-25 Added analog read function, as well as some test code for it.
2016-12-02 Test Code
2016-12-02 Uploading Casey's code
2016-12-03 Added DEBUG option
2016-12-03 More debugging over USART enabled.
2016-12-03 Moved analog read functions to analog.c. Included WARNING above DEBUG def. Included note in MIDITEST that MIDI is confirmed to work using our HW configuration.
2016-12-03 updated boms
2016-12-04 removed reference to semiconductor library
2016-12-04 formatting
2016-12-04 Created AnalogRead_MeanPCx functions in analog.c.
2016-12-07 organizational changes
2016-12-07 unnecessary _
2016-12-07 updated gantt
2016-12-07 Buttons to allow manual calibration
2016-12-07 Sensor 1 Calibration working
2016-12-07 Sensor 2 working
2016-12-07 Sensor 3 Calibration working
2016-12-07 All 3 calibration sequences confirmed working successively.
2016-12-07 Sensor1 Calibration with LED indicator working.
2016-12-07 Sensor 2 Calibration with LED indicator working.
2016-12-07 Sensor 3 Calibration with LED indicators working.
2016-12-07 All 3 sensor calibrations with LED indicators working, with MIDI Initialized.
2016-12-07 Moved global variables to main.h. Created defines for passed values to calibration function.
2016-12-07 Mode switching capability added. Confirmed ability to switch between modes, including calibration, which still works properly.
2016-12-07 Moved button press code to buttons.c. Tested button press code, mode switching, LED indicators and Calibration. All working.
2016-12-08 Mostly working mode 1
2016-12-08 Working, no MEAN, no velocity logarithm
2016-12-08 Mean for pitch working
2016-12-08 New MEAN working
2016-12-08 Added presentation. Good job Everyone!
